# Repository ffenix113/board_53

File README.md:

# board_53

An Arduino Nano-sized board based on [nRF5340](https://www.nordicsemi.com/Products/nRF5340).
Idea is to have modern and accessible alternative to a sea of nRF52840 boards.

## Features
* Similar, but not identical, pinout to [Arduino Nano 33 BLE](https://docs.arduino.cc/hardware/nano-33-ble/).
* Based on Raytac [MDBT53-1M](https://www.raytac.com/product/ins.php?index_id=121) (nRF5340).
* USB-C connector.
* RGB LED.
* Uses TI [TPS62291](https://www.ti.com/lit/ds/symlink/tps62293.pdf) for better efficiency. This also allows to use batteries in 2.3-6.0 V range (no on-board charger).
* Two buttons: Reset & User configurable.
* SWD pins on the edges.
* Chip antena for better wireless.
* Rather easy to solder this board at home.

## Notes
1. This board is not (yet?) available in Zephyr. Zephyr board definition from this repository should be used when building for this board.
2. Board will be revisioned to improve & simplify design.
3. Buck converter is used to improve efficiency, but maybe will be converted for LDO in next revisions.
4. Bootloader is not required, but MCUBoot can be used as one. UF2 bootloader is not currently (15 Dec, 2024) available for nRF53.
5. There are 0402 resistors in revision 0.1, which will be replaced by 0603(or even 0804) in next revision for easier placing & soldering.

## Contact
* For issues and proposals please use Issues.
* For direct contact please use: board_53@ffenix113.addy.io

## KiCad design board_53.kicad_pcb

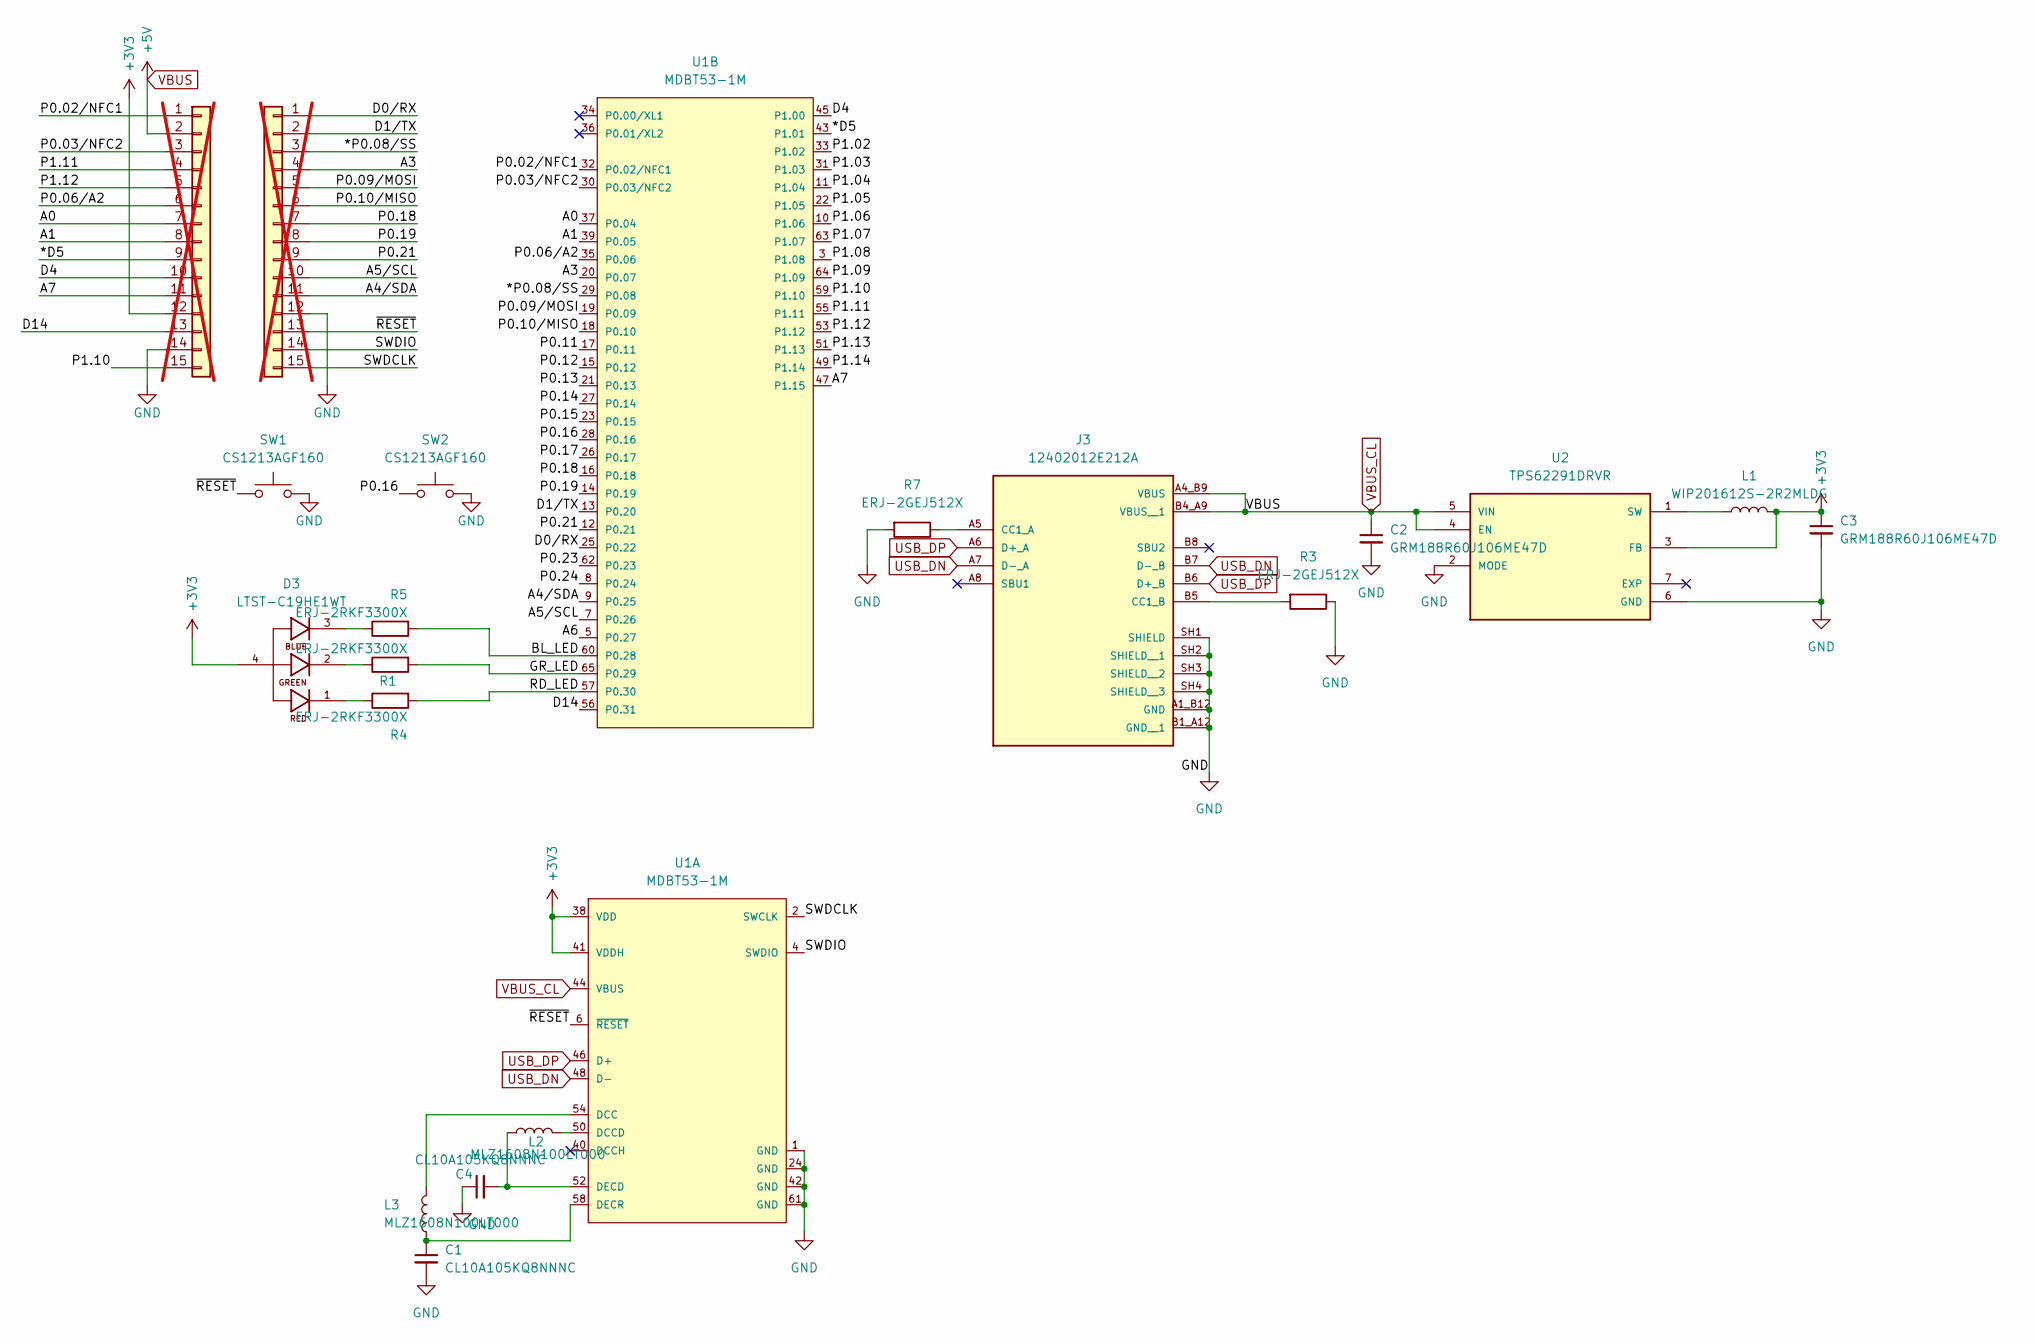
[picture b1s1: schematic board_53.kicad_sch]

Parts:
C1, C4: CL10A105KQ8NNNC; C_0603_1608Metric_Pad1.08x0.95mm_HandSolder
C2, C3: GRM188R60J106ME47D; C_0603_1608Metric_Pad1.08x0.95mm_HandSolder
D3: LTST-C19HE1WT; LED_LiteOn_LTST-C19HE1WT; PARTREV B
J1: Analog; PinHeader_1x15_P2.54mm_Vertical; not fitted
J2: Digital; PinHeader_1x15_P2.54mm_Vertical; not fitted
J3: 12402012E212A; AMPHENOL_12402012E212A; PARTREV 4
L1: WIP201612S-2R2MLDG; L_0805_2012Metric_Pad1.15x1.40mm_HandSolder
L2, L3: MLZ1608N100LT000; L_0603_1608Metric_Pad1.05x0.95mm_HandSolder
R1, R4, R5: ERJ-2RKF3300X; R_0402_1005Metric_Pad0.72x0.64mm_HandSolder
R3, R7: ERJ-2GEJ512X; R_0402_1005Metric_Pad0.72x0.64mm_HandSolder
SW1, SW2: CS1213AGF160; SW_CS1213AGF260_CRS
U1: MDBT53-1M; Raytac-MDBT53-1M-MFG; digikey description NORDIC NRF5340 CHIP ANTENNA MODU
U2: TPS62291DRVR; WSON-6-1EP_2x2mm_P0.65mm_EP1x1.6mm_ThermalVias; PARTREV G

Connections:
+3V3: C3.1, D3.4, J1.12, L1.2, U1.38 (VDD), U1.41 (VDDH), U2.3 (FB)
/*D5: J1.9, U1.43 (P1.01)
/*P0.08/SS: J2.3, U1.29 (P0.08)
/A0: J1.7, U1.37 (P0.04)
/A1: J1.8, U1.39 (P0.05)
/A3: J2.4, U1.20 (P0.07)
/A4/SDA: J2.11, U1.9 (P0.25)
/A5/SCL: J2.10, U1.7 (P0.26)
/A6: U1.5 (P0.27)
/A7: J1.11, U1.47 (P1.15)
/BL_LED: R5.2, U1.60 (P0.28)
/D0/RX: J2.1, U1.25 (P0.22)
/D1/TX: J2.2, U1.13 (P0.20)
/D4: J1.10, U1.45 (P1.00)
/D14: J1.13, U1.56 (P0.31)
/GR_LED: R1.2, U1.65 (P0.29)
/P0.02/NFC1: J1.1, U1.32 (P0.02/NFC1)
/P0.03/NFC2: J1.3, U1.30 (P0.03/NFC2)
/P0.06/A2: J1.6, U1.35 (P0.06)
/P0.09/MOSI: J2.5, U1.19 (P0.09)
/P0.10/MISO: J2.6, U1.18 (P0.10)
/P0.11: U1.17 (P0.11)
/P0.12: U1.15 (P0.12)
/P0.13: U1.21 (P0.13)
/P0.14: U1.27 (P0.14)
/P0.15: U1.23 (P0.15)
/P0.16: SW2.1, U1.28 (P0.16)
/P0.17: U1.26 (P0.17)
/P0.18: J2.7, U1.16 (P0.18)
/P0.19: J2.8, U1.14 (P0.19)
/P0.21: J2.9, U1.12 (P0.21)
/P0.23: U1.62 (P0.23)
/P0.24: U1.8 (P0.24)
/P1.02: U1.33 (P1.02)
/P1.03: U1.31 (P1.03)
/P1.04: U1.11 (P1.04)
/P1.05: U1.22 (P1.05)
/P1.06: U1.10 (P1.06)
/P1.07: U1.63 (P1.07)
/P1.08: U1.3 (P1.08)
/P1.09: U1.64 (P1.09)
/P1.10: J1.15, U1.59 (P1.10)
/P1.11: J1.4, U1.55 (P1.11)
/P1.12: J1.5, U1.53 (P1.12)
/P1.13: U1.51 (P1.13)
/P1.14: U1.49 (P1.14)
/RD_LED: R4.2, U1.57 (P0.30)
/SWDCLK: J2.15, U1.2 (SWCLK)
/SWDIO: J2.14, U1.4 (SWDIO)
/~RESET: J2.13, SW1.1, U1.6 (~RESET)
GND: C1.2, C2.2, C3.2, C4.1, J1.14, J2.12, J3.A1_B12 (GND), J3.B1_A12 (GND__1), J3.SH1 (SHIELD), J3.SH2 (SHIELD__1), J3.SH3 (SHIELD__2), J3.SH4 (SHIELD__3), R3.1, R7.2, SW1.2, SW2.2, U1.1 (GND), U1.24 (GND), U1.42 (GND), U1.61 (GND), U2.2 (MODE), U2.6 (GND)
unnamed: D3.1, R4.1
unnamed: D3.2, R1.1
unnamed: D3.3, R5.1
unnamed: J3.A5 (CC1_A), R7.1
unnamed: J3.B5 (CC1_B), R3.2
unnamed: L3.2, U1.54 (DCC)
unnamed: L2.2, U1.50 (DCCD)
unnamed: C4.2, L2.1, U1.52 (DECD)
unnamed: C1.1, L3.1, U1.58 (DECR)
unnamed: L1.1, U2.1 (SW)
USB_DN: J3.A7 (D-_A), J3.B7 (D-_B), U1.48 (D-)
USB_DP: J3.A6 (D+_A), J3.B6 (D+_B), U1.46 (D+)
VBUS: C2.1, J1.2, J3.A4_B9 (VBUS), J3.B4_A9 (VBUS__1), U1.44 (VBUS), U2.4 (EN), U2.5 (VIN)

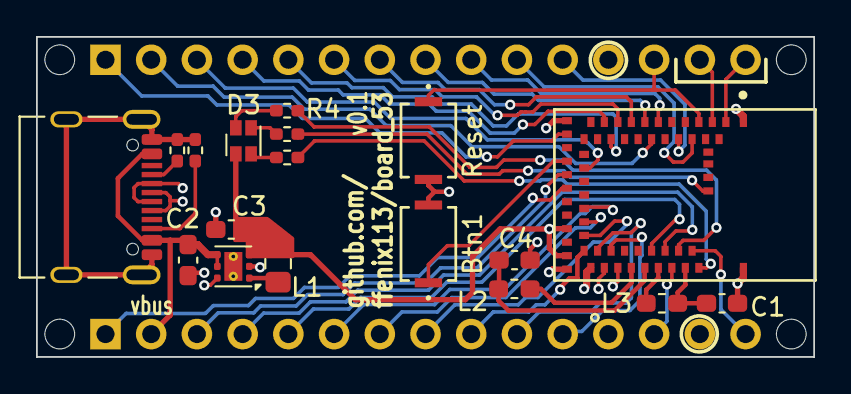
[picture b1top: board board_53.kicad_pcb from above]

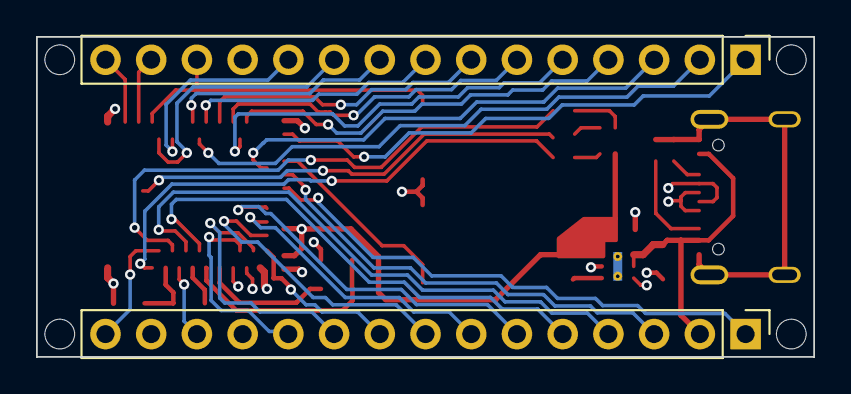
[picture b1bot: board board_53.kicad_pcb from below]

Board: 4 copper layers, 43.2 x 17.8 mm, 24 parts (2 on the bottom side), 45 nets.

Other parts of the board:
MH1, MH2, MH3, MH4: MountingHole_65mil

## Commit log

2024-10-06 Init files for Board_53
2024-12-15 Init commit
2024-12-28 dev ci
2024-12-28 dev ci (#1)
2025-09-12 add zephyr & openocd definitions
2025-09-12 add schematic pdf
